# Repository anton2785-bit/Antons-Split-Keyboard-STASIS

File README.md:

# Antons-Split-Keyboard-STASIS
---
## What is this project
* This is a split keyboard. That means that it has 2 separarate parts   that are conected to the PC via bluethooth. This allows them to have separate layouts and to have the opportunity to be in different places whiie typing. 
---
## Why i made this project/split keyboard

* I wanted to have a small portable keyboard that I can still use for typing and to be compact. 
---
  ## Images
  * This is an image of the schematic:
  * 

  * This is the PCB:
  * 

  * The 3D model of the PCB:
  * 
  * The case with half of the keyboard:
  * 

  ---
  
  ## Assembly

* First I need to soulder everything to the PCB
* Then I need to upload a test code that will let me see what switch is what signals.
* Before it being done you need to put the now done assembly into the case. 
* After that I upload the real code and I am happy to use it afterwards.
  
  ---
  
 ## BOM
| Component | Purpose | Qty | Unit Cost | Total | Distributor |
|-----------|---------|-----|-----------|-------|-------------|
| [Keycaps](https://www.aliexpress.com/item/1005010519485476.html) | Low-profile keycaps | 1 set | — | $16.68 | AliExpress |
| [Resistors](https://www.aliexpress.com/item/1005010519485476.html) | Battery voltage divider (806kΩ + 1MΩ) | 1 set | — | $4.32 | AliExpress |
| [Gateron Hotswap Sockets](https://www.gateron.com/products/gateron-low-profile-switch-hot-swap-pcb-socket?VariantsId=10234) | Low-profile hotswap | 1 set | — | $7.00 | Gateron |
| [Gateron KS-33 Switches](https://www.gateron.com/products/gateron-ks-33-low-profile-20-banana-switch?VariantsId=10734) | Low-profile banana switches | 2 sets | — | $19.60 | Gateron |
| [PCB](https://jlcpcb.com) | Reversible split PCB (JLCPCB) | 1 set | — | $35.00 | JLCPCB |
| [Seeed XIAO nRF52840](https://www.seeedstudio.com/Seeed-XIAO-BLE-nRF52840-p-5201.html) | Wireless MCU, one per half | 2 | $17.00 | $34.00 | Seeed Studio |

---
## Credits

* Designed and built by *(Anton/ Anton-2785-bit)
* Inspired by open‑source mechanical keyboard and hackpad communities (https://stasis.hackclub.com/dashboard).

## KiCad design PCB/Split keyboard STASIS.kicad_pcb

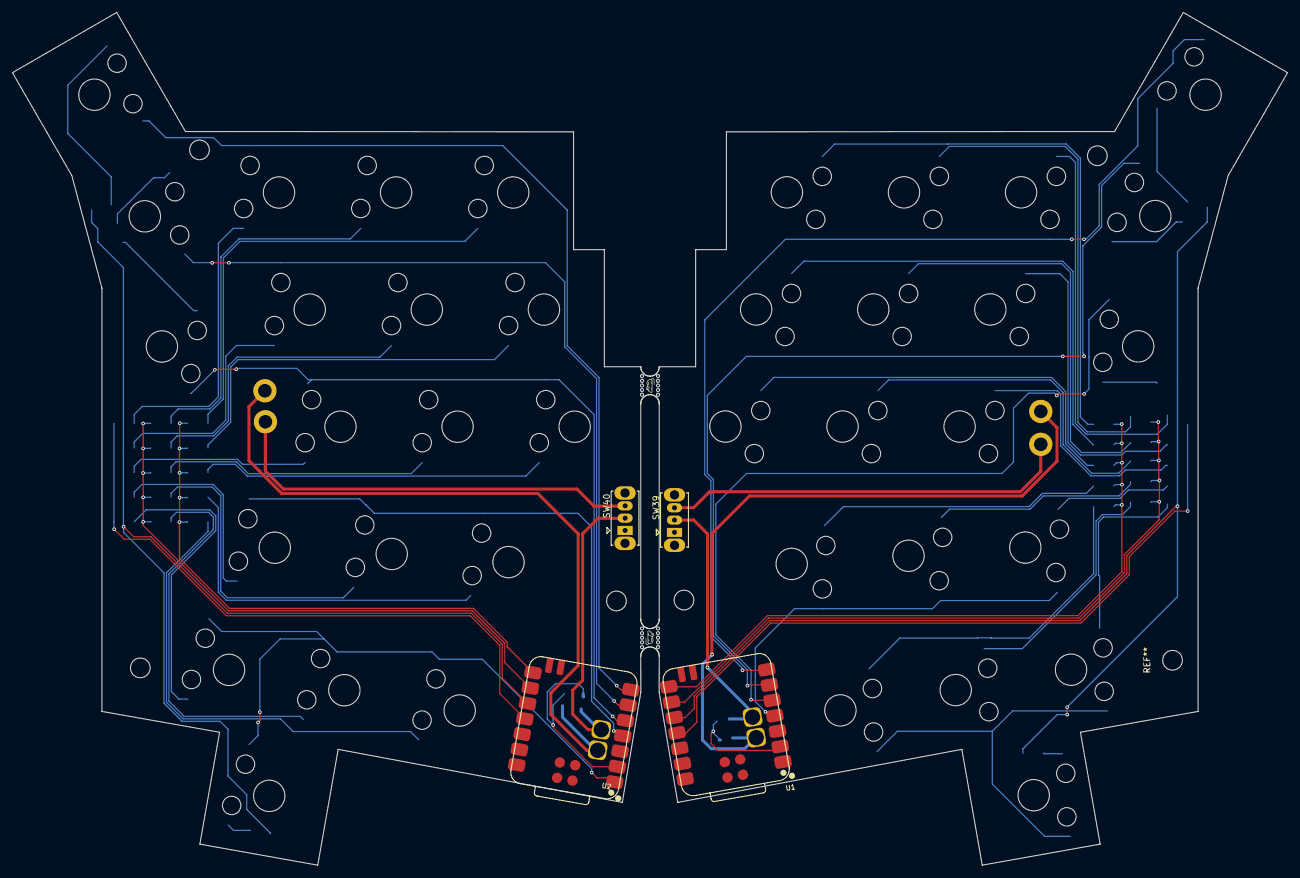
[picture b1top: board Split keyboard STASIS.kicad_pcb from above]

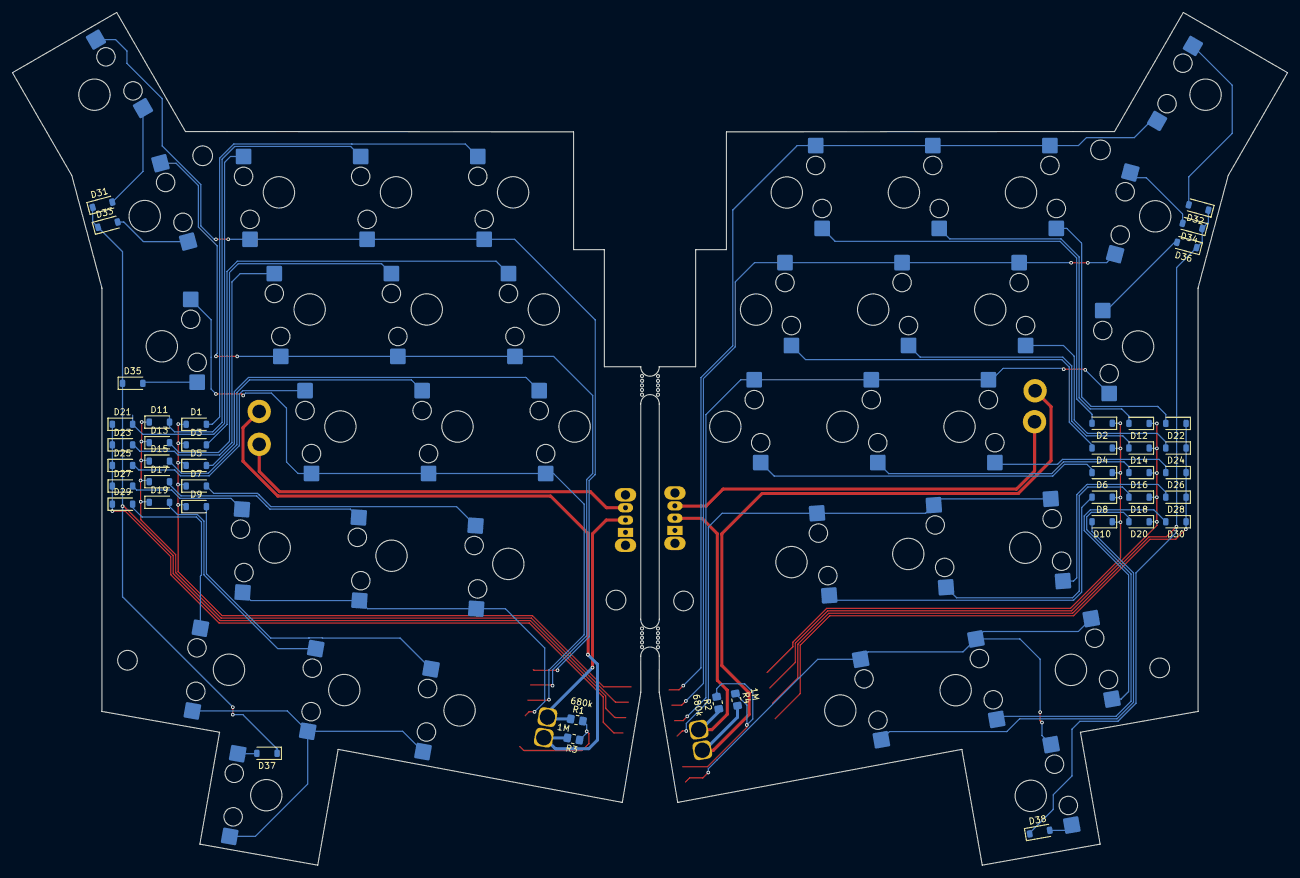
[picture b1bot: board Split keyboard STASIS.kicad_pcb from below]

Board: 2 copper layers, 207.4 x 138.7 mm, 90 parts (80 on the bottom side), 52 nets.

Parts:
B1, B2: MouseBite; mouse-bite-3mm-6mm
D1, D2, D3, D4, D5, D6, D7, D8, D9, D10, D11, D12, D13, D14, D15, D16, D17, D18, D19, D20, D21, D22, D23, D24, D25, D26, D27, D28, D29, D30, D31, D32, D33, D34, D35, D36, D37, D38: 1N4148W; D_SOD-123
J1, J2, J3, J4: Conn_01x01_Pin; MountingHole_2.2mm_M2_DIN965_Pad
R1, R2: 680k; R_0805_2012Metric_Pad1.20x1.40mm_HandSolder
R3, R4: 1M; R_0805_2012Metric_Pad1.20x1.40mm_HandSolder
SW1, SW2, SW3, SW4, SW5, SW6, SW7, SW8, SW9, SW10, SW11, SW12, SW13, SW14, SW15, SW16, SW17, SW18, SW19, SW20, SW21, SW22, SW23, SW24, SW25, SW26, SW27, SW28, SW29, SW30, SW31, SW32, SW33, SW34, SW35, SW36, SW37, SW38: SW_Push_45deg; Gateron-KS33-Hotswap-1U
SW39, SW40: SW_Push_SPDT; SW_Slide_SPDT_Straight_CK_OS102011MS2Q
U1, U2: XIAO-nRF52840-SMD; modified-XIAO-nRF52840-SMD

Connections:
Bat +: R1.1, R2.1, SW39.2 (B), SW40.2 (B), U1.15 (BAT), U2.15 (BAT)
Bat pin +: R1.2, R2.2, R3.1, R4.1, U1.2 (P0.03_A1_D1), U2.2 (P0.03_A1_D1)
C1: SW1.1, SW2.1, SW11.1, SW12.1, SW21.1, SW22.1, SW31.1, SW32.1, U1.7 (P1.11_D6_TX), U2.7 (P1.11_D6_TX)
C2: SW3.1, SW4.1, SW13.1, SW14.1, SW23.1, SW24.1, SW33.1, SW34.1, U1.6 (P0.05_A5_D5_SCL), U2.6 (P0.05_A5_D5_SCL)
C3: SW5.1, SW6.1, SW15.1, SW16.1, SW25.1, SW26.1, SW35.1, SW36.1, U1.5 (P0.04_A4_D4_SDA), U2.5 (P0.04_A4_D4_SDA)
C4: SW7.1, SW8.1, SW17.1, SW18.1, SW27.1, SW28.1, U1.4 (P0.29_A3_D3), U2.4 (P0.29_A3_D3)
C5: SW9.1, SW10.1, SW19.1, SW20.1, SW29.1, SW30.1, SW37.1, SW38.1, U1.1 (P0.02_A0_D0), U2.1 (P0.02_A0_D0)
GND: J3.1, J4.1, R3.2, R4.2, U1.13 (GND), U1.16 (GND), U2.13 (GND), U2.16 (GND)
unnamed: D1.2 (A), SW1.2
unnamed: D2.2 (A), SW2.2
unnamed: D3.2 (A), SW3.2
unnamed: D4.2 (A), SW4.2
unnamed: D5.2 (A), SW5.2
unnamed: D6.2 (A), SW6.2
unnamed: D7.2 (A), SW7.2
unnamed: D8.2 (A), SW8.2
unnamed: D9.2 (A), SW9.2
unnamed: D10.2 (A), SW10.2
unnamed: D11.2 (A), SW11.2
unnamed: D12.2 (A), SW12.2
unnamed: D13.2 (A), SW13.2
unnamed: D14.2 (A), SW14.2
unnamed: D15.2 (A), SW15.2
unnamed: D16.2 (A), SW16.2
unnamed: D17.2 (A), SW17.2
unnamed: D18.2 (A), SW18.2
unnamed: D19.2 (A), SW19.2
unnamed: D20.2 (A), SW20.2
unnamed: D21.2 (A), SW21.2
unnamed: D22.2 (A), SW22.2
unnamed: D23.2 (A), SW23.2
unnamed: D24.2 (A), SW24.2
unnamed: D25.2 (A), SW25.2
unnamed: D26.2 (A), SW26.2
unnamed: D27.2 (A), SW27.2
unnamed: D28.2 (A), SW28.2
unnamed: D29.2 (A), SW29.2
unnamed: D30.2 (A), SW30.2
unnamed: D31.2 (A), SW31.2
unnamed: D32.2 (A), SW32.2
unnamed: D33.2 (A), SW33.2
unnamed: D34.2 (A), SW34.2
unnamed: D35.2 (A), SW35.2
unnamed: D36.2 (A), SW36.2
unnamed: D37.2 (A), SW37.2
unnamed: D38.2 (A), SW38.2
unnamed: J1.1, SW40.3 (C)
unnamed: J2.1, SW39.3 (C)
R1: D1.1 (K), D2.1 (K), D3.1 (K), D4.1 (K), D5.1 (K), D6.1 (K), D7.1 (K), D8.1 (K), D9.1 (K), D10.1 (K), U1.8 (P1.12_D7_RX), U2.8 (P1.12_D7_RX)
R2: D11.1 (K), D12.1 (K), D13.1 (K), D14.1 (K), D15.1 (K), D16.1 (K), D17.1 (K), D18.1 (K), D19.1 (K), D20.1 (K), U1.9 (P1.13_D8_SCK), U2.9 (P1.13_D8_SCK)
R3: D21.1 (K), D22.1 (K), D23.1 (K), D24.1 (K), D25.1 (K), D26.1 (K), D27.1 (K), D28.1 (K), D29.1 (K), D30.1 (K), U1.11 (P1.15_D10_MOSI), U2.11 (P1.15_D10_MOSI)
R4: D31.1 (K), D32.1 (K), D33.1 (K), D34.1 (K), D35.1 (K), D36.1 (K), D37.1 (K), D38.1 (K), U1.10 (P1.14_D9_MISO), U2.10 (P1.14_D9_MISO)

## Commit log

2026-04-09 File update
